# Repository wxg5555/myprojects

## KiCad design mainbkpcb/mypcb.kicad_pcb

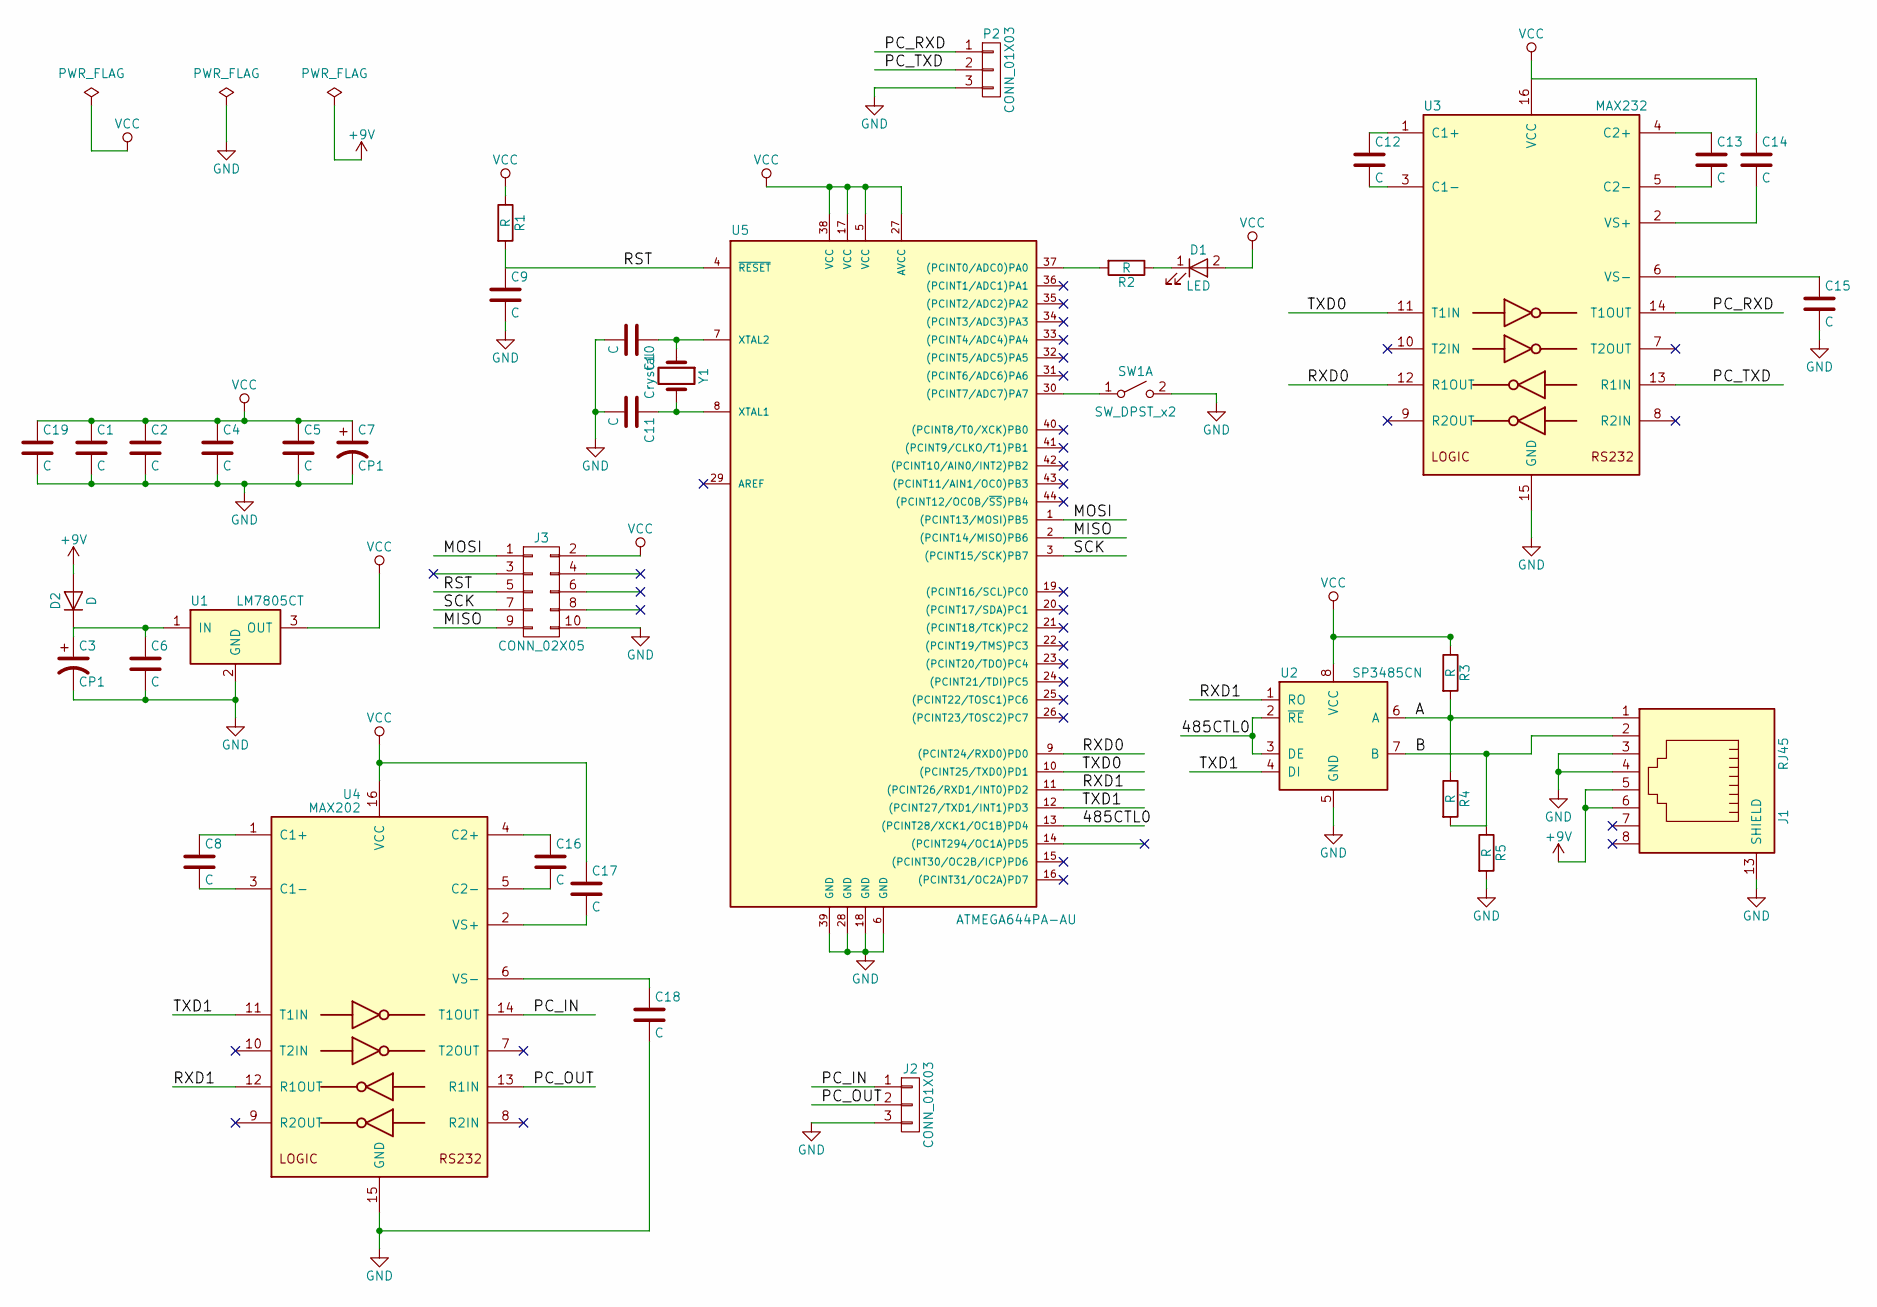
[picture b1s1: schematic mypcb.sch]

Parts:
C1, C2, C4, C5, C10, C11, C12, C13, C14, C15: C; C_0805_HandSoldering
C3, C7: CP1; CP_Elec_6.3x4.5
C6, C8, C16, C17, C18, C19: C; C_0805
C9: C; C_1206_HandSoldering
D1: LED; D_SOD-123F
D2: D; D_SOD-123F
J1: RJ45; RJ45_TRANSFO
J2: CONN_01X03; Pin_Header_Straight_1x03_Pitch2.54mm
J3: CONN_02X05; IDC_Header_Straight_10pins
P2: CONN_01X03; Pin_Header_Straight_1x03
R1, R2, R3, R4, R5: R; R_0805_HandSoldering
SW1: SW_DPST_x2; SW_SPST_EVQPE1
U1: LM7805CT; TO-220_Vertical
U2: SP3485CN; SOIC-8_3.9x4.9mm_Pitch1.27mm
U3: MAX232; SOIC-16_3.9x9.9mm_Pitch1.27mm
U4: MAX202; SOIC-16_3.9x9.9mm_Pitch1.27mm
U5: ATMEGA644PA-AU; LQFP-44_10x10mm_Pitch0.8mm
Y1: Crystal; Crystal_SMD_HC49-SD

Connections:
+9V: D2.2 (A), J1.5, J1.6
/485CTL0: U2.2 (~RE~), U2.3 (DE), U5.13 ((PCINT28/XCK1/OC1B)PD4)
/A: J1.1, R3.2, R4.1, U2.6 (A)
/B: J1.2, R4.2, R5.1, U2.7 (B)
/MISO: J3.9, U5.2 ((PCINT14/MISO)PB6)
/MOSI: J3.1, U5.1 ((PCINT13/MOSI)PB5)
/PC_IN: J2.1, U4.14 (T1OUT)
/PC_OUT: J2.2, U4.13 (R1IN)
/PC_RXD: P2.1, U3.14 (T1OUT)
/PC_TXD: P2.2, U3.13 (R1IN)
/RST: C9.1, J3.5, R1.2, U5.4 (~RESET)
/RXD0: U3.12 (R1OUT), U5.9 ((PCINT24/RXD0)PD0)
/RXD1: U2.1 (RO), U4.12 (R1OUT), U5.11 ((PCINT26/RXD1/INT0)PD2)
/SCK: J3.7, U5.3 ((PCINT15/SCK)PB7)
/TXD0: U3.11 (T1IN), U5.10 ((PCINT25/TXD0)PD1)
/TXD1: U2.4 (DI), U4.11 (T1IN), U5.12 ((PCINT27/TXD1/INT1)PD3)
GND: C1.2, C2.2, C3.2, C4.2, C5.2, C6.2, C7.2, C9.2, C10.2, C11.2, C15.2, C18.2, C19.2, J1.3, J1.4, J1.13 (SHIELD), J2.3, J3.10, P2.3, R5.2, SW1.2 (B), U1.2 (GND), U2.5 (GND), U3.15 (GND), U4.15 (GND), U5.6 (GND), U5.18 (GND), U5.28 (GND), U5.39 (GND)
unnamed: C3.1, C6.1, D2.1 (K), U1.1 (IN)
unnamed: C8.1, U4.1 (C1+)
unnamed: C8.2, U4.3 (C1-)
unnamed: C10.1, U5.7 (XTAL2), Y1.1
unnamed: C11.1, U5.8 (XTAL1), Y1.2
unnamed: C12.1, U3.1 (C1+)
unnamed: C12.2, U3.3 (C1-)
unnamed: C13.1, U3.4 (C2+)
unnamed: C13.2, U3.5 (C2-)
unnamed: C14.2, U3.2 (VS+)
unnamed: C15.1, U3.6 (VS-)
unnamed: C16.1, U4.4 (C2+)
unnamed: C16.2, U4.5 (C2-)
unnamed: C17.2, U4.2 (VS+)
unnamed: C18.1, U4.6 (VS-)
unnamed: D1.1 (K), R2.1
unnamed: R2.2, U5.37 ((PCINT0/ADC0)PA0)
unnamed: SW1.1 (A), U5.30 ((PCINT7/ADC7)PA7)
VCC: C1.1, C2.1, C4.1, C5.1, C7.1, C14.1, C17.1, C19.1, D1.2 (A), J3.2, R1.1, R3.1, U1.3 (OUT), U2.8 (VCC), U3.16 (VCC), U4.16 (VCC), U5.5 (VCC), U5.17 (VCC), U5.27 (AVCC), U5.38 (VCC)

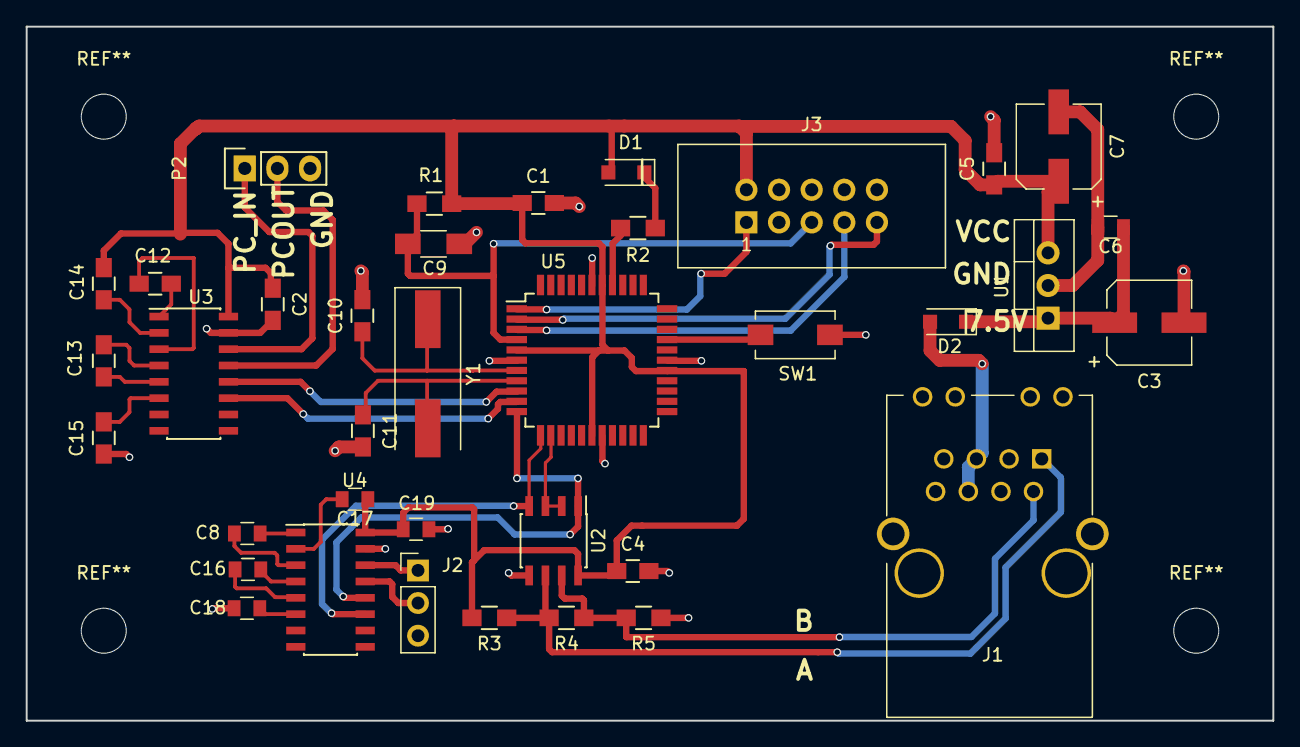
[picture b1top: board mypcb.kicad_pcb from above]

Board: 2 copper layers, 97.0 x 54.0 mm, 37 parts (0 on the bottom side), 36 nets.

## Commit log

2017-08-10 CHANGE RJ45 Y1 LED C data
